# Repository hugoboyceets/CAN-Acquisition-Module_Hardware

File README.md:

# CAN-Acquisition-Module_Hardware

It's a data acquisition module that can communicate to a PC (and to other modules) over CANbus. This allows for cheap & rugged hardware, as well as simplified wiring and long transmission distances.

At it's core is a Nuvoton M483 microcontroller (ARM Cortex-M4F). It has 8 thermistor inputs, 4 multipurpose analog inputs, and room to accomodate CO2 and/or humidity sensors over I2C or UART.

It can be configured & monitored over USB (it enumerates as a COM port adapter), and a basic screen is present to facilitate human identification and debugging.

The repository for the firmware can be found [here](https://github.com/hboyce4/CAN-Acquisition-Module_Firmware).
The repository the the PC server program can be found [here](https://github.com/hugoboyceets/CAN-Acquisition-Module_Server).

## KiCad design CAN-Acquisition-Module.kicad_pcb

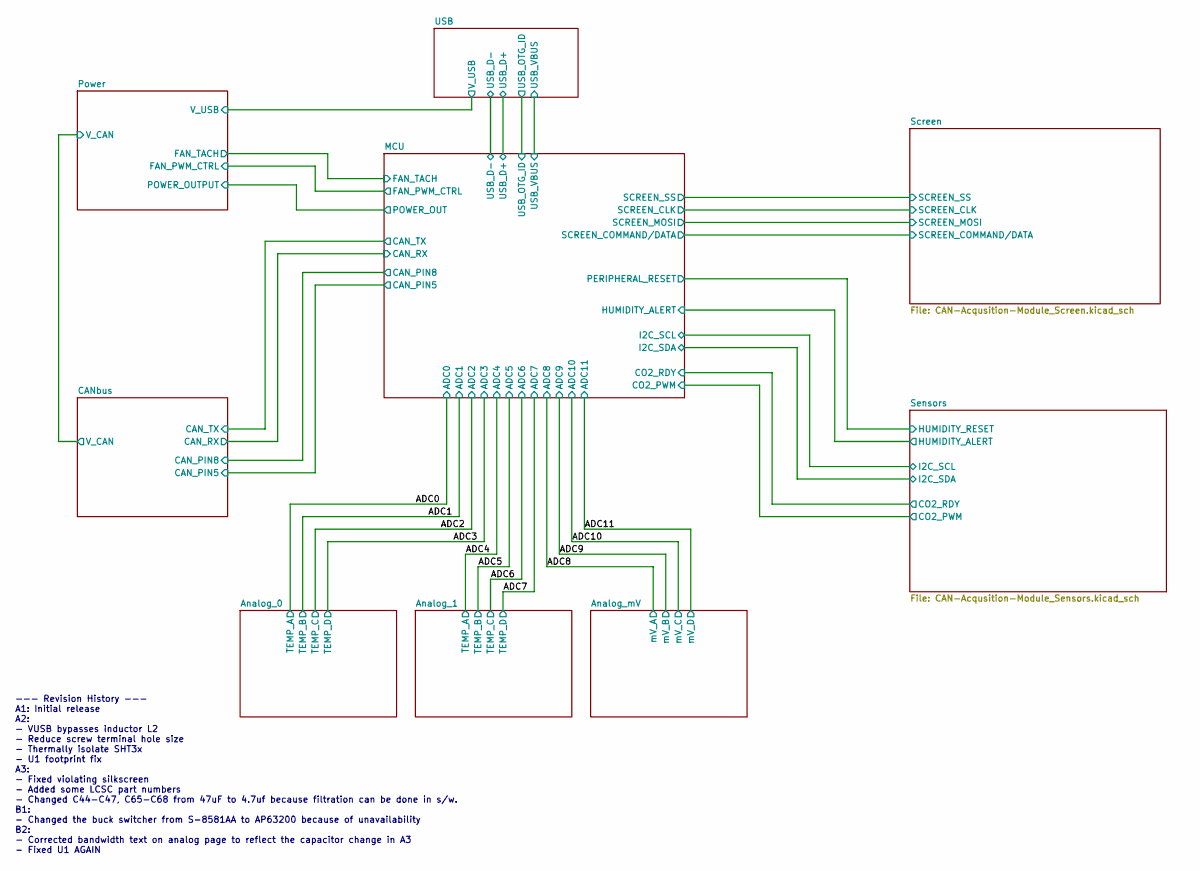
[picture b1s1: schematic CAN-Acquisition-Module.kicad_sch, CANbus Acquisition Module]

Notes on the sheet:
--- Revision History --- A1: Initial release A2: - VUSB bypasses inductor L2 - Reduce screw terminal hole size - Thermally isolate SHT3x - U1 footprint fix A3: - Fixed violating silkscreen - Added some LCSC part numbers - Changed C44-C47, C65-C68 from 47uF to 4.7uf because filtration can be done in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

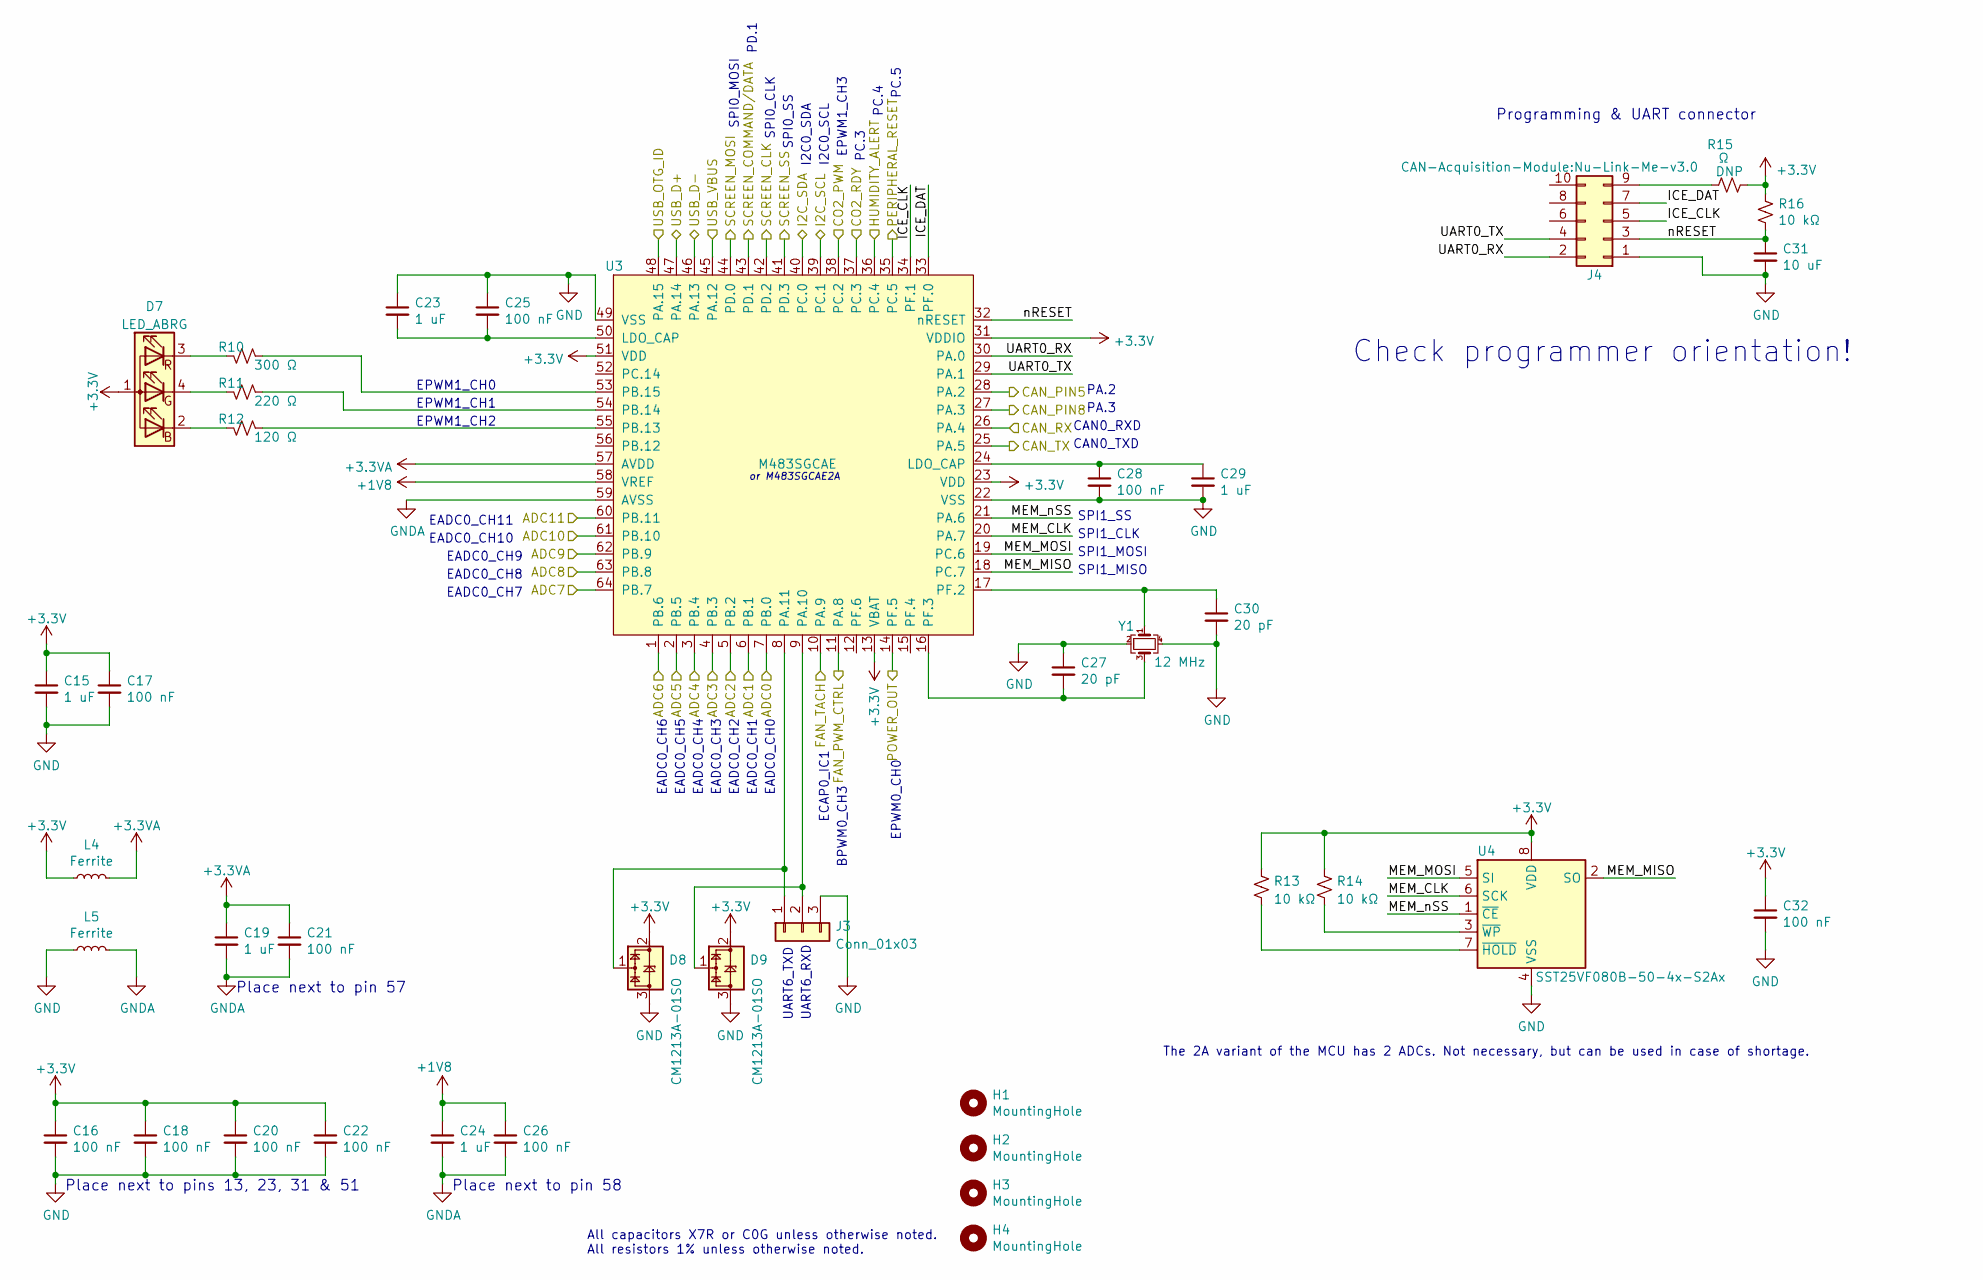
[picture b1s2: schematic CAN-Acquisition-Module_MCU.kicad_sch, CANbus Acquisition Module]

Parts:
C15, C19, C23, C24, C29: 1 uF; C_0603_1608Metric; Rated Voltage 25V; LCSC P/N C386079
C16, C17, C18, C20, C21, C22, C25, C26, C28, C32: 100 nF; C_0402_1005Metric; Rated Voltage 16V; LCSC P/N C77014
C27, C30: 20 pF; C_0603_1608Metric; LCSC P/N C123543
C31: 10 uF; C_0805_2012Metric; Rated Voltage 6.3V; LCSC P/N C386019
D7: LED_ABRG; LED_RGB_Wuerth-PLCC4_3.2x2.8mm_150141M173100; LCSC P/N C409779
D8, D9: CM1213A-01SO; SOT-23; LCSC P/N C558429
H1, H2, H3, H4: MountingHole; MountingHole_3.2mm_M3; LCSC P/N DNP
J3: Conn_01x03; PinSocket_1x03_P2.54mm_Vertical; LCSC P/N DNP
J4: Conn_02x05_Odd_Even; Nu-Link-Me-v3.0; LCSC P/N C124387
L4, L5: Ferrite; L_0603_1608Metric; LCSC P/N C96995
R10: 300 Ω; R_0603_1608Metric; Tolerance 1%; LCSC P/N C114617
R11: 220 Ω; R_0603_1608Metric; Tolerance 1%; LCSC P/N C22962
R12: 120 Ω; R_0603_1608Metric; Tolerance 1%; LCSC P/N C22787
R13, R14, R16: 10 kΩ; R_0603_1608Metric; Tolerance 1%; LCSC P/N C98220
R15: Ω; R_0603_1608Metric; LCSC P/N DNP
U3: M483SGCAE; LQFP-64_7x7mm_P0.4mm; LCSC P/N C3231235
U4: SST25VF080B-50-4x-S2Ax; SOIC-8_P1.27mm_Multi; LCSC P/N DNP
Y1: 12 MHz; Crystal_SMD_3225-4Pin_3.2x2.5mm; LCSC P/N C91749

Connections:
+1V8: C24.1, C26.1, U3.58 (VREF); also elsewhere on the board
+3.3VA: C19.1, C21.1, L4.2, U3.57 (AVDD); also elsewhere on the board
+3V3: C15.1, C16.1, C17.1, C18.1, C20.1, C22.1, C32.1, D7.1 (A), D8.2 (VP), D9.2 (VP), L4.1, R13.1, R14.1, R15.2, R16.1, U3.13 (VBAT), U3.23 (VDD), U3.31 (VDDIO), U3.51 (VDD), U4.8 (VDD); also elsewhere on the board
/ADC0: U3.7 (PB.0); also elsewhere on the board
/ADC1: U3.6 (PB.1); also elsewhere on the board
/ADC2: U3.5 (PB.2); also elsewhere on the board
/ADC3: U3.4 (PB.3); also elsewhere on the board
/ADC4: U3.3 (PB.4); also elsewhere on the board
/ADC5: U3.2 (PB.5); also elsewhere on the board
/ADC6: U3.1 (PB.6); also elsewhere on the board
/ADC7: U3.64 (PB.7); also elsewhere on the board
/ADC8: U3.63 (PB.8); also elsewhere on the board
/ADC9: U3.62 (PB.9); also elsewhere on the board
/ADC10: U3.61 (PB.10); also elsewhere on the board
/ADC11: U3.60 (PB.11); also elsewhere on the board
/CANbus/CAN_PIN5: U3.28 (PA.2); also elsewhere on the board
/CANbus/CAN_PIN8: U3.27 (PA.3); also elsewhere on the board
/CANbus/CAN_RX: U3.26 (PA.4); also elsewhere on the board
/CANbus/CAN_TX: U3.25 (PA.5); also elsewhere on the board
/MCU/CO2_PWM: U3.38 (PC.2); also elsewhere on the board
/MCU/CO2_RDY: U3.37 (PC.3); also elsewhere on the board
/MCU/FAN_PWM_CTRL: U3.11 (PA.8); also elsewhere on the board
/MCU/FAN_TACH: U3.10 (PA.9); also elsewhere on the board
/MCU/HUMIDITY_ALERT: U3.36 (PC.4); also elsewhere on the board
/MCU/I2C_SCL: U3.39 (PC.1); also elsewhere on the board
/MCU/I2C_SDA: U3.40 (PC.0); also elsewhere on the board
/MCU/ICE_CLK: J4.5, U3.34 (PF.1)
/MCU/ICE_DAT: J4.7, U3.33 (PF.0)
/MCU/MEM_CLK: U3.20 (PA.7), U4.6 (SCK)
/MCU/MEM_MISO: U3.18 (PC.7), U4.2 (SO)
/MCU/MEM_MOSI: U3.19 (PC.6), U4.5 (SI)
/MCU/MEM_nSS: U3.21 (PA.6), U4.1 (~CE)
/MCU/PERIPHERAL_RESET: U3.35 (PC.5); also elsewhere on the board
/MCU/POWER_OUT: U3.14 (PF.5); also elsewhere on the board
/MCU/SCREEN_CLK: U3.42 (PD.2); also elsewhere on the board
/MCU/SCREEN_COMMAND/DATA: U3.43 (PD.1); also elsewhere on the board
/MCU/SCREEN_MOSI: U3.44 (PD.0); also elsewhere on the board
/MCU/SCREEN_SS: U3.41 (PD.3); also elsewhere on the board
/MCU/UART0_RX: J4.2, U3.30 (PA.0)
/MCU/UART0_TX: J4.4, U3.29 (PA.1)
/MCU/USB_D+: U3.47 (PA.14); also elsewhere on the board
/MCU/USB_D-: U3.46 (PA.13); also elsewhere on the board
/MCU/USB_OTG_ID: U3.48 (PA.15); also elsewhere on the board
/MCU/USB_VBUS: U3.45 (PA.12); also elsewhere on the board
/MCU/nRESET: C31.1, J4.3, R16.2, U3.32 (nRESET)
GND: C15.2, C16.2, C17.2, C18.2, C20.2, C22.2, C23.1, C25.1, C27.1, C28.2, C29.2, C30.2, C31.2, C32.2, D8.3 (VN), D9.3 (VN), J3.3, J4.1, L5.1, U3.22 (VSS), U3.49 (VSS), U4.4 (VSS), Y1.2, Y1.4; also elsewhere on the board
GNDA: C19.2, C21.2, C24.2, C26.2, L5.2, U3.59 (AVSS); also elsewhere on the board
unnamed: C23.2, C25.2, U3.50 (LDO_CAP)
unnamed: C27.2, U3.16 (PF.3), Y1.3
unnamed: C28.1, C29.1, U3.24 (LDO_CAP)
unnamed: C30.1, U3.17 (PF.2), Y1.1
unnamed: D7.2 (BK), R12.2
unnamed: D7.3 (RK), R10.2
unnamed: D7.4 (GK), R11.2
unnamed: D8.1 (CH1), J3.1, U3.8 (PA.11)
unnamed: D9.1 (CH1), J3.2, U3.9 (PA.10)
unnamed: J4.9, R15.1
unnamed: R10.1, U3.53 (PB.15)
unnamed: R11.1, U3.54 (PB.14)
unnamed: R12.1, U3.55 (PB.13)
unnamed: R13.2, U4.7 (~HOLD)
unnamed: R14.2, U4.3 (~WP)

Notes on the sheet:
PD.1
I2C0_SDA
SPI1_CLK
Programming & UART connector
PA.3
EADC0_CH9
EPWM1_CH3
EADC0_CH5
Place next to pins 13, 23, 31 & 51
EADC0_CH10
SPI0_SS
The 2A variant of the MCU has 2 ADCs. Not necessary, but can be used in case of shortage.
EPWM1_CH0
PC.5
PC.3
EADC0_CH6
ECAP0_IC1
CAN0_RXD
CAN0_TXD
Place next to pin 58
SPI0_MOSI
EADC0_CH0
Check programmer orientation!
UART6_RXD
PC.4
EPWM1_CH1
UART6_TXD
All capacitors X7R or C0G unless otherwise noted. All resistors 1% unless otherwise noted.
Place next to pin 57
EPWM0_CH0
SPI1_MISO
EADC0_CH7
or M483SGCAE2A
BPWM0_CH3
EADC0_CH8
EADC0_CH1
EADC0_CH2
EPWM1_CH2
EADC0_CH4
SPI0_CLK

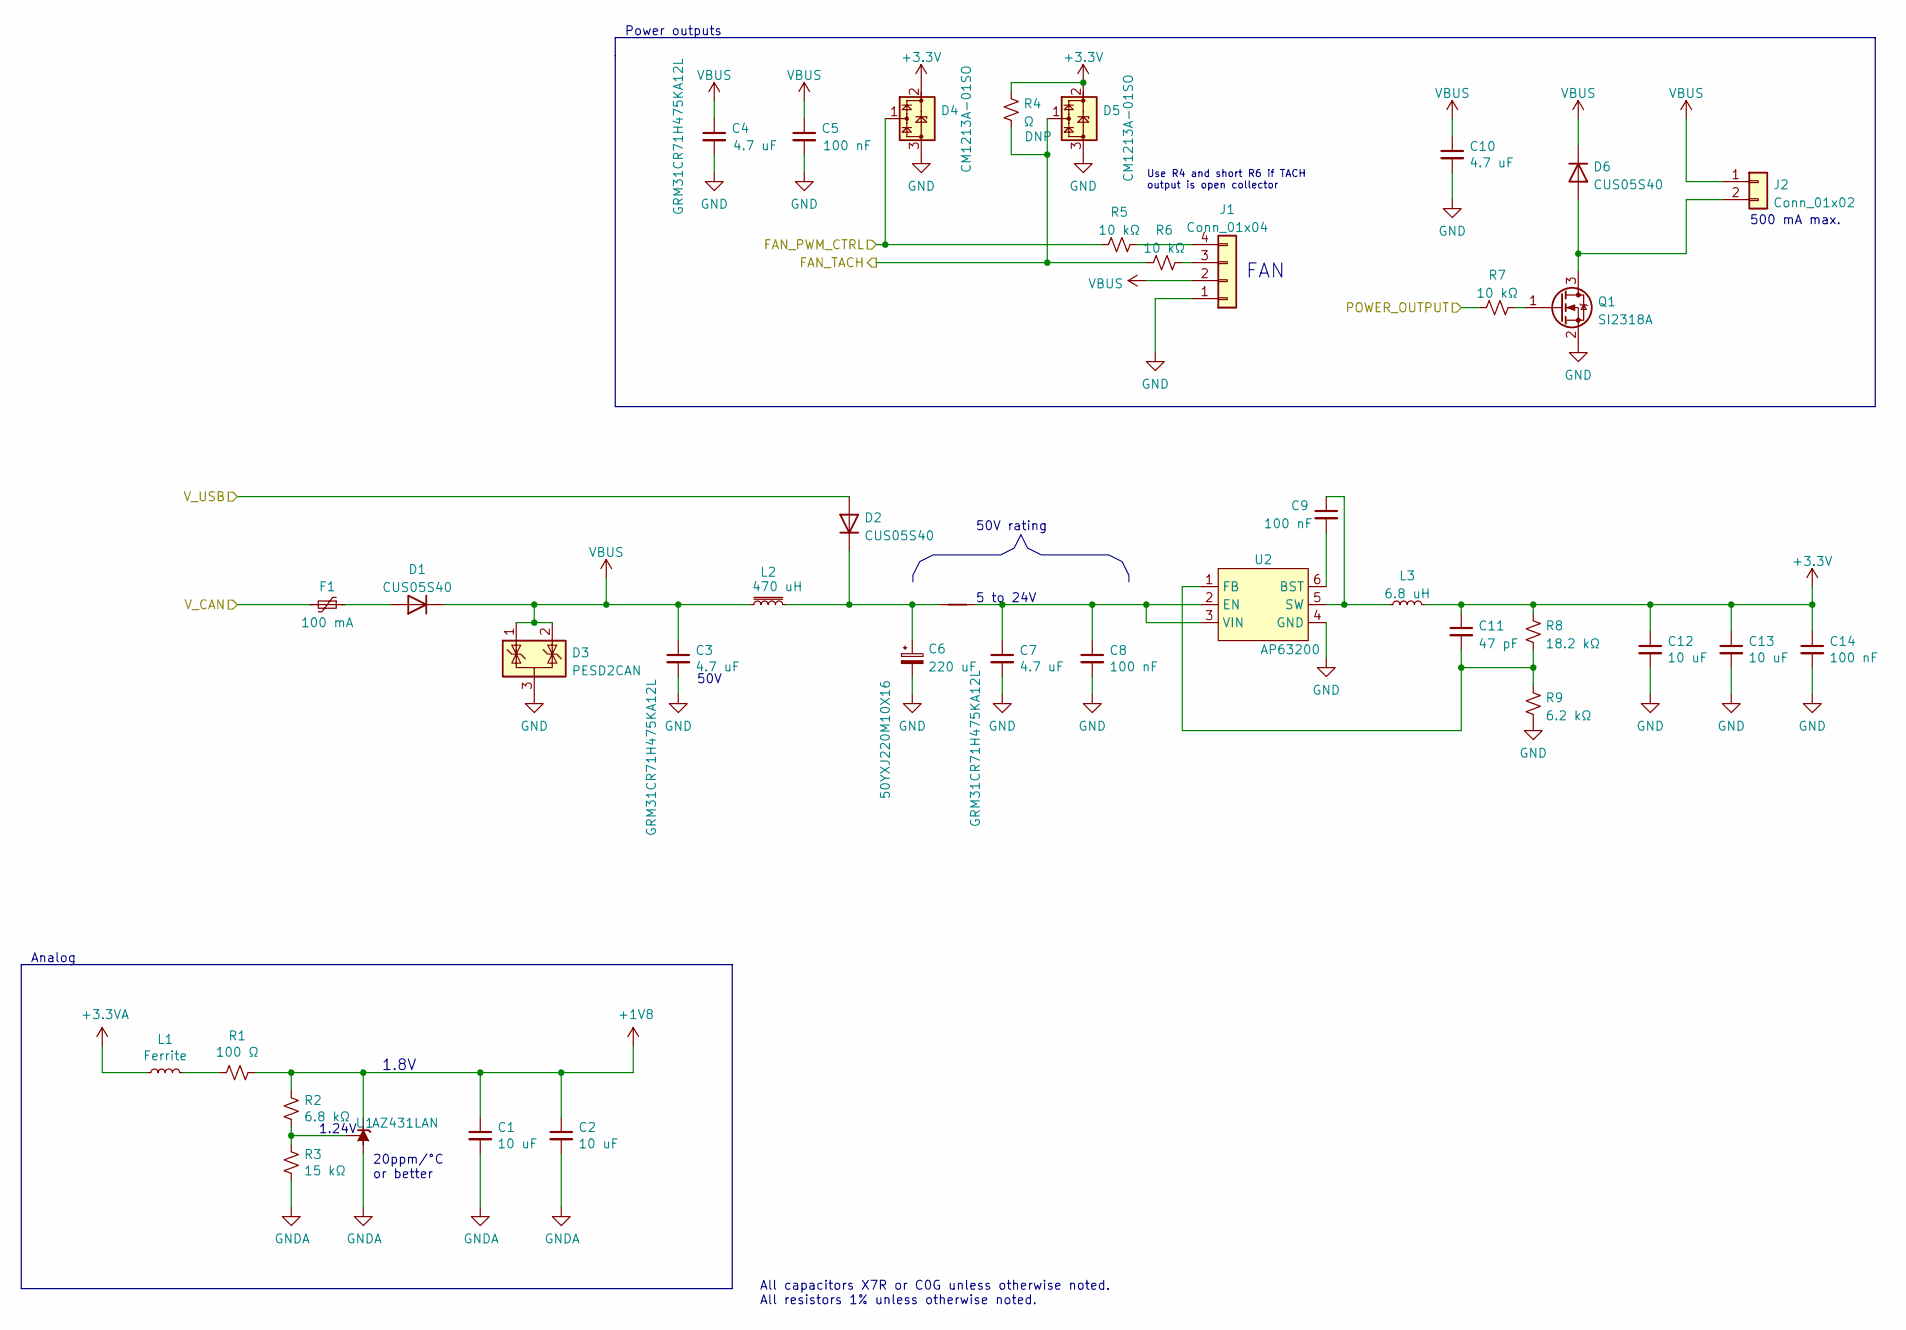
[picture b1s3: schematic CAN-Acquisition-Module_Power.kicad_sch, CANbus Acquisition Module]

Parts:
C1, C2, C12, C13: 10 uF; C_0805_2012Metric; Rated Voltage 6.3V; LCSC P/N C386019
C3, C4, C7, C10: 4.7 uF; C_1206_3216Metric; Rated Voltage 50V; LCSC P/N C92853
C5, C8, C9: 100 nF; C_0603_1608Metric; Rated Voltage 50V; LCSC P/N C314282
C6: 220 uF; CP_Radial_D10.0mm_P5.00mm_Horizontal; Rated Voltage 50V; LCSC P/N DNP
C11: 47 pF; C_0603_1608Metric; LCSC P/N C126580
C14: 100 nF; C_0402_1005Metric; Rated Voltage 16V; LCSC P/N C77014
D1, D2, D6: CUS05S40; Toshiba_USC; LCSC P/N C2762696
D3: PESD2CAN; SOT-23; LCSC P/N C284078
D4, D5: CM1213A-01SO; SOT-23; LCSC P/N C558429
F1: 100 mA; Fuse_1206_3216Metric; LCSC P/N C70065
J1: Conn_01x04; FanPinHeader_1x04_P2.54mm_Vertical; LCSC P/N DNP
J2: Conn_01x02; PinHeader_1x02_P2.54mm_Vertical; LCSC P/N DNP
L1: Ferrite; L_0603_1608Metric; LCSC P/N C96995
L2: 470 uH; Murata_LQH43_1812(4532_Metric); LCSC P/N C394141
L3: 6.8 uH; Murata_LQH3_1212(3030_Metric); LCSC P/N C703775
NT1: NetTie_2; Net_Tie_small; LCSC P/N DNP
Q1: SI2318A; SOT-23; LCSC P/N DNP
R1: 100 Ω; R_0805_2012Metric; Tolerance 5%; LCSC P/N C17408
R2: 6.8 kΩ; R_0603_1608Metric; Tolerance 0.1%; LCSC P/N C55912
R3: 15 kΩ; R_0603_1608Metric; Tolerance 0.1%; LCSC P/N C60590
R4: Ω; R_0603_1608Metric; LCSC P/N DNP
R5, R6, R7: 10 kΩ; R_0603_1608Metric; Tolerance 1%; LCSC P/N C98220
R8: 18.2 kΩ; R_0603_1608Metric; Tolerance 1%; LCSC P/N C22892
R9: 6.2 kΩ; R_0805_2012Metric; Tolerance 0.1%; LCSC P/N C351551
U1: AZ431LAN; SOT-23; LCSC P/N C460576
U2: AP63200; Diodes-Inc_TSOT26; LCSC P/N C2071868

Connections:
+1V8: C1.1, C2.1, R1.1, R2.1, U1.2 (K); also elsewhere on the board
+3.3VA: L1.1; also elsewhere on the board
+3V3: C11.1, C12.1, C13.1, C14.1, D4.2 (VP), D5.2 (VP), L3.2, R4.2, R8.1; also elsewhere on the board
/CANbus/V+/RED: F1.2; also elsewhere on the board
/MCU/FAN_PWM_CTRL: D4.1 (CH1), R5.1; also elsewhere on the board
/MCU/FAN_TACH: D5.1 (CH1), R4.1, R6.1; also elsewhere on the board
/MCU/POWER_OUT: R7.1; also elsewhere on the board
/Power/V_USB: D2.2 (A); also elsewhere on the board
GND: C3.2, C4.2, C5.2, C6.2, C7.2, C8.2, C10.2, C12.2, C13.2, C14.2, D3.3 (A), D4.3 (VN), D5.3 (VN), J1.1, Q1.2 (S), R9.2, U2.4 (GND); also elsewhere on the board
GNDA: C1.2, C2.2, R3.2, U1.3 (A); also elsewhere on the board
unnamed: C6.1, D2.1 (K), L2.2, NT1.1
unnamed: C7.1, C8.1, NT1.2, U2.2 (EN), U2.3 (VIN)
unnamed: C9.1, L3.1, U2.5 (SW)
unnamed: C9.2, U2.6 (BST)
unnamed: C11.2, R8.2, R9.1, U2.1 (FB)
unnamed: D1.2 (A), F1.1
unnamed: D6.2 (A), J2.2, Q1.3 (D)
unnamed: J1.3, R6.2
unnamed: J1.4, R5.2
unnamed: L1.2, R1.2
unnamed: Q1.1 (G), R7.2
unnamed: R2.2, R3.1, U1.1 (REF)
VBUS: C3.1, C4.1, C5.1, C10.1, D1.1 (K), D3.1 (K), D3.2 (K), D6.1 (K), J1.2, J2.1, L2.1

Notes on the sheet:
50V
5 to 24V
1.8V
FAN
Power outputs
Analog
All capacitors X7R or C0G unless otherwise noted. All resistors 1% unless otherwise noted.
Use R4 and short R6 if TACH output is open collector
1.24V
50V rating
500 mA max.
20ppm/°C or better

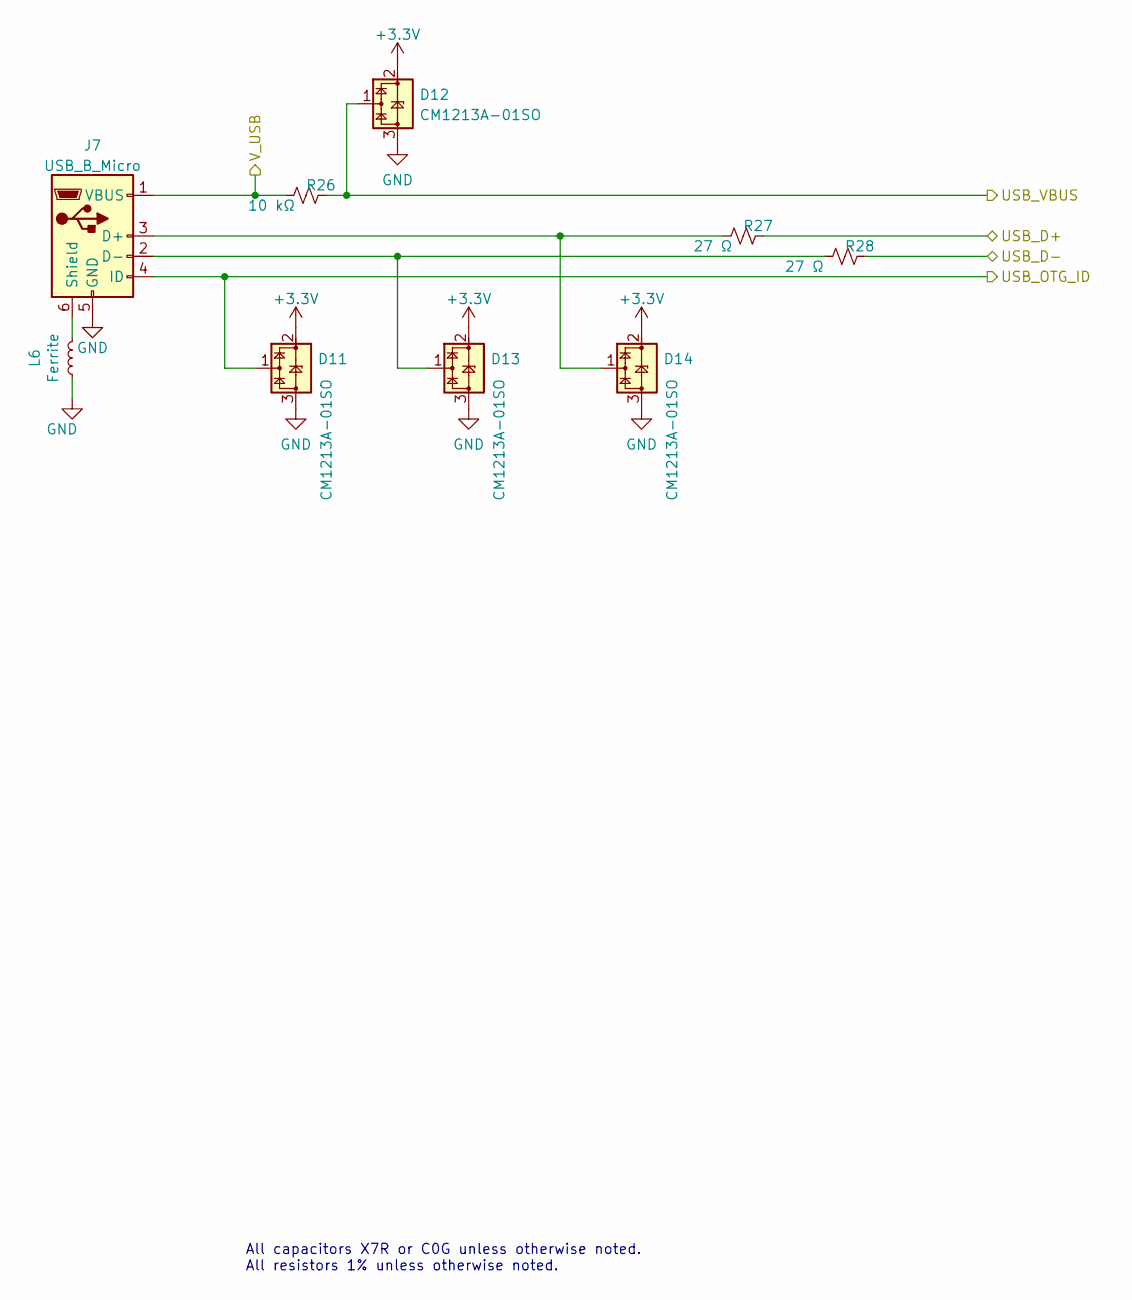
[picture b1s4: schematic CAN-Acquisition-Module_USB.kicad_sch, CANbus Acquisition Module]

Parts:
D11, D12, D13, D14: CM1213A-01SO; SOT-23; LCSC P/N C558429
J7: USB_B_Micro; GCT-USB3131-30-0230-A; LCSC P/N C920231
L6: Ferrite; L_0603_1608Metric; LCSC P/N C96995
R26: 10 kΩ; R_0603_1608Metric; Tolerance 1%; LCSC P/N C98220
R27, R28: 27 Ω; R_0603_1608Metric; Tolerance 1%; LCSC P/N C25190

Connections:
+3V3: D11.2 (VP), D12.2 (VP), D13.2 (VP), D14.2 (VP); also elsewhere on the board
/MCU/USB_D+: R27.2; also elsewhere on the board
/MCU/USB_D-: R28.2; also elsewhere on the board
/MCU/USB_OTG_ID: D11.1 (CH1), J7.4 (ID); also elsewhere on the board
/MCU/USB_VBUS: D12.1 (CH1), R26.2; also elsewhere on the board
/Power/V_USB: J7.1 (VBUS), R26.1; also elsewhere on the board
GND: D11.3 (VN), D12.3 (VN), D13.3 (VN), D14.3 (VN), J7.5 (GND), L6.1; also elsewhere on the board
unnamed: D13.1 (CH1), J7.2 (D-), R28.1
unnamed: D14.1 (CH1), J7.3 (D+), R27.1
unnamed: J7.6 (Shield), L6.2

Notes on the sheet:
All capacitors X7R or C0G unless otherwise noted. All resistors 1% unless otherwise noted.

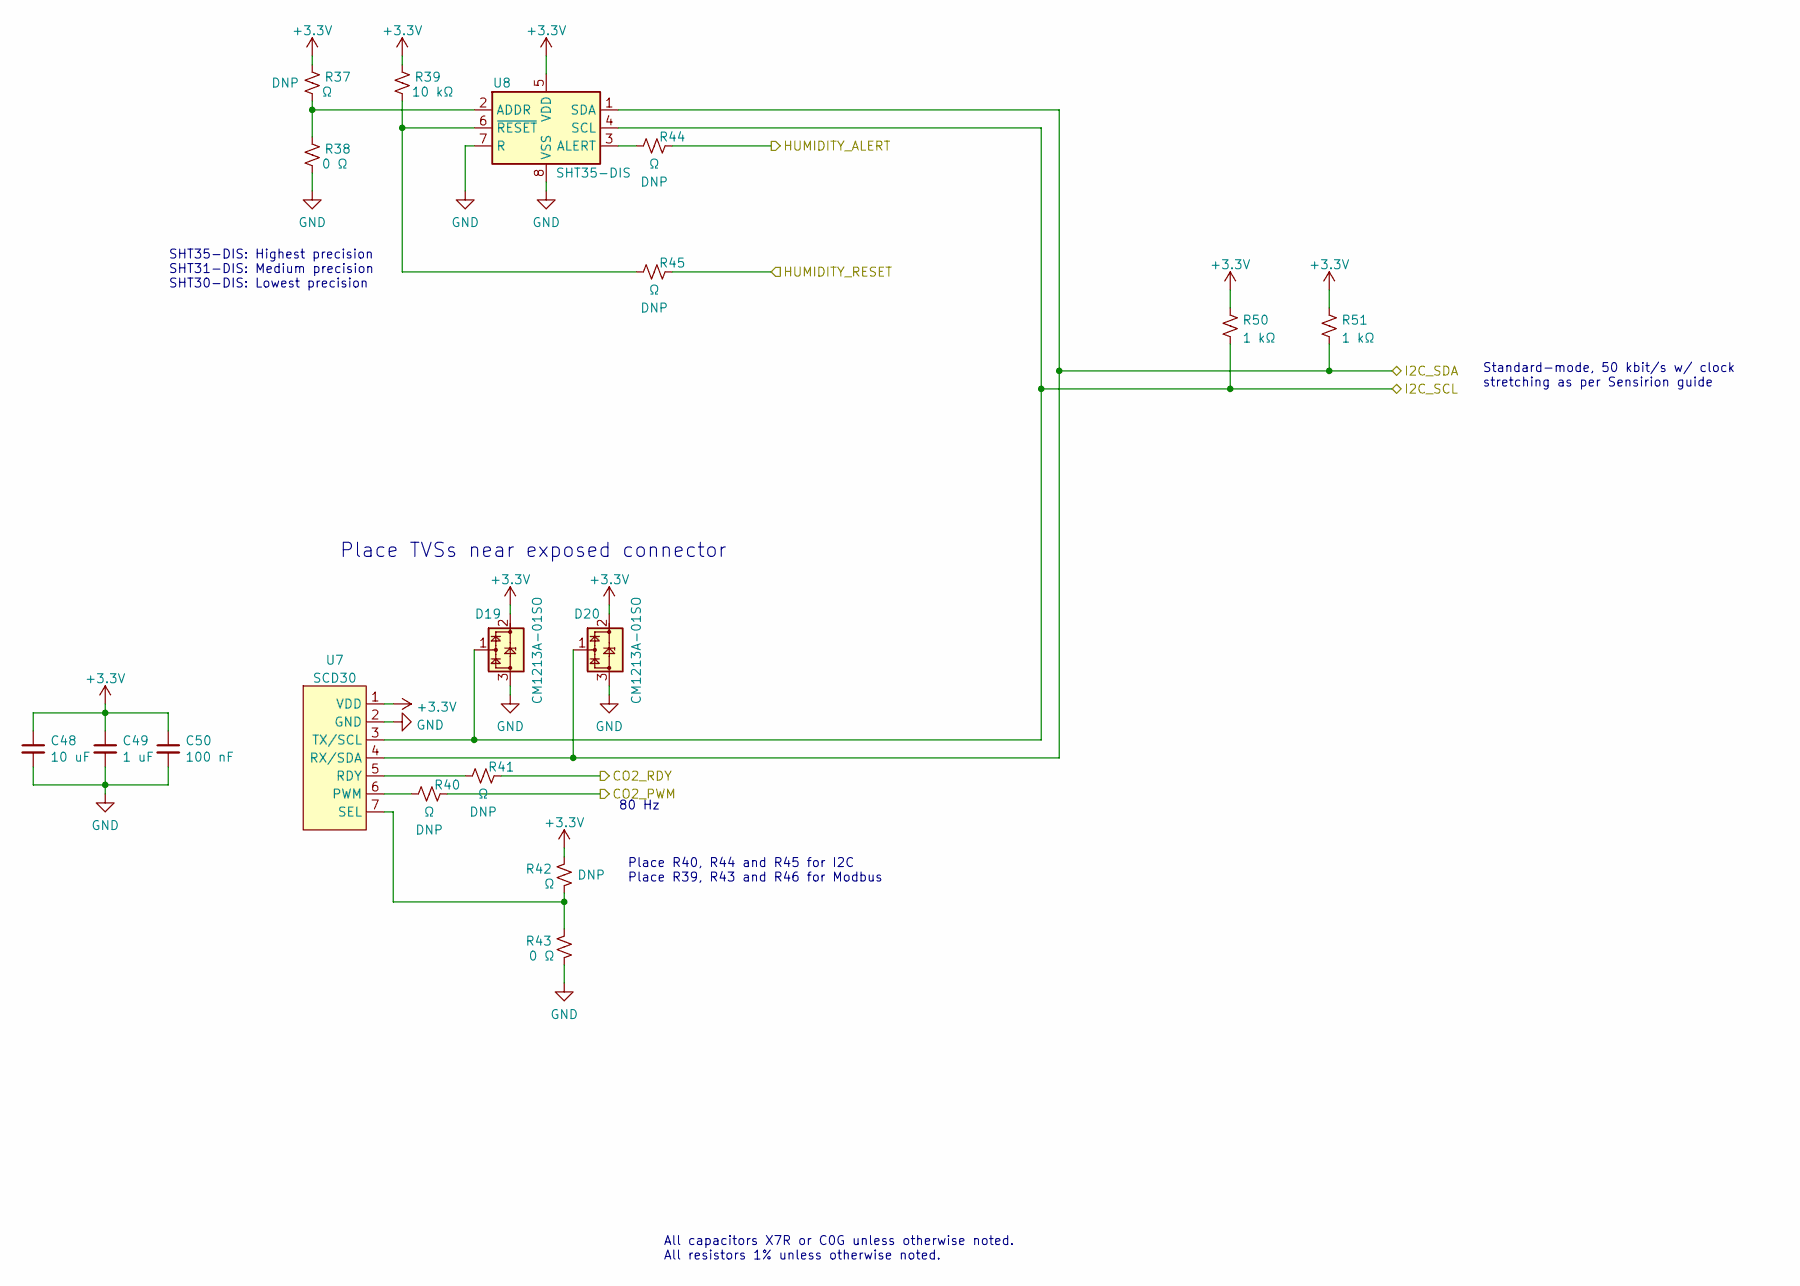
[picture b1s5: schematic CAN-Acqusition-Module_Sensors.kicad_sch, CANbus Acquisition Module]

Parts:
C48: 10 uF; C_0805_2012Metric; Rated Voltage 6.3V; LCSC P/N C386019
C49: 1 uF; C_0603_1608Metric; Rated Voltage 25V; LCSC P/N C386079
C50: 100 nF; C_0402_1005Metric; Rated Voltage 16V; LCSC P/N C77014
D19, D20: CM1213A-01SO; SOT-23; LCSC P/N C558429
R37, R40, R41, R42, R44, R45: Ω; R_0603_1608Metric; LCSC P/N DNP
R38, R43: 0 Ω; R_0603_1608Metric; Tolerance 1%; LCSC P/N C21189
R39: 10 kΩ; R_0603_1608Metric; Tolerance 1%; LCSC P/N C98220
R50, R51: 1 kΩ; R_0603_1608Metric; Tolerance 1%; LCSC P/N C22548
U7: SCD30; LCSC P/N DNP
U8: SHT35-DIS; Sensirion_DFN-8-1EP_2.5x2.5mm_P0.5mm_EP1.1x1.7mm; LCSC P/N DNP

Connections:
+3V3: C48.1, C49.1, C50.1, D19.2 (VP), D20.2 (VP), R37.1, R39.1, R42.1, R50.1, R51.1, U7.1 (VDD), U8.5 (VDD); also elsewhere on the board
/MCU/CO2_PWM: R40.2; also elsewhere on the board
/MCU/CO2_RDY: R41.2; also elsewhere on the board
/MCU/HUMIDITY_ALERT: R44.2; also elsewhere on the board
/MCU/I2C_SCL: D19.1 (CH1), R50.2, U7.3 (TX/SCL), U8.4 (SCL); also elsewhere on the board
/MCU/I2C_SDA: D20.1 (CH1), R51.2, U7.4 (RX/SDA), U8.1 (SDA); also elsewhere on the board
/MCU/PERIPHERAL_RESET: R45.2; also elsewhere on the board
GND: C48.2, C49.2, C50.2, D19.3 (VN), D20.3 (VN), R38.2, R43.2, U7.2 (GND), U8.7 (R), U8.8 (VSS), U8.9 (VSS); also elsewhere on the board
unnamed: R37.2, R38.1, U8.2 (ADDR)
unnamed: R39.2, R45.1, U8.6 (~RESET)
unnamed: R40.1, U7.6 (PWM)
unnamed: R41.1, U7.5 (RDY)
unnamed: R42.2, R43.1, U7.7 (SEL)
unnamed: R44.1, U8.3 (ALERT)

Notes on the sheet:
80 Hz
SHT35-DIS: Highest precision SHT31-DIS: Medium precision SHT30-DIS: Lowest precision
All capacitors X7R or C0G unless otherwise noted. All resistors 1% unless otherwise noted.
Place R40, R44 and R45 for I2C Place R39, R43 and R46 for Modbus
Standard-mode, 50 kbit/s w/ clock stretching as per Sensirion guide
Place TVSs near exposed connector

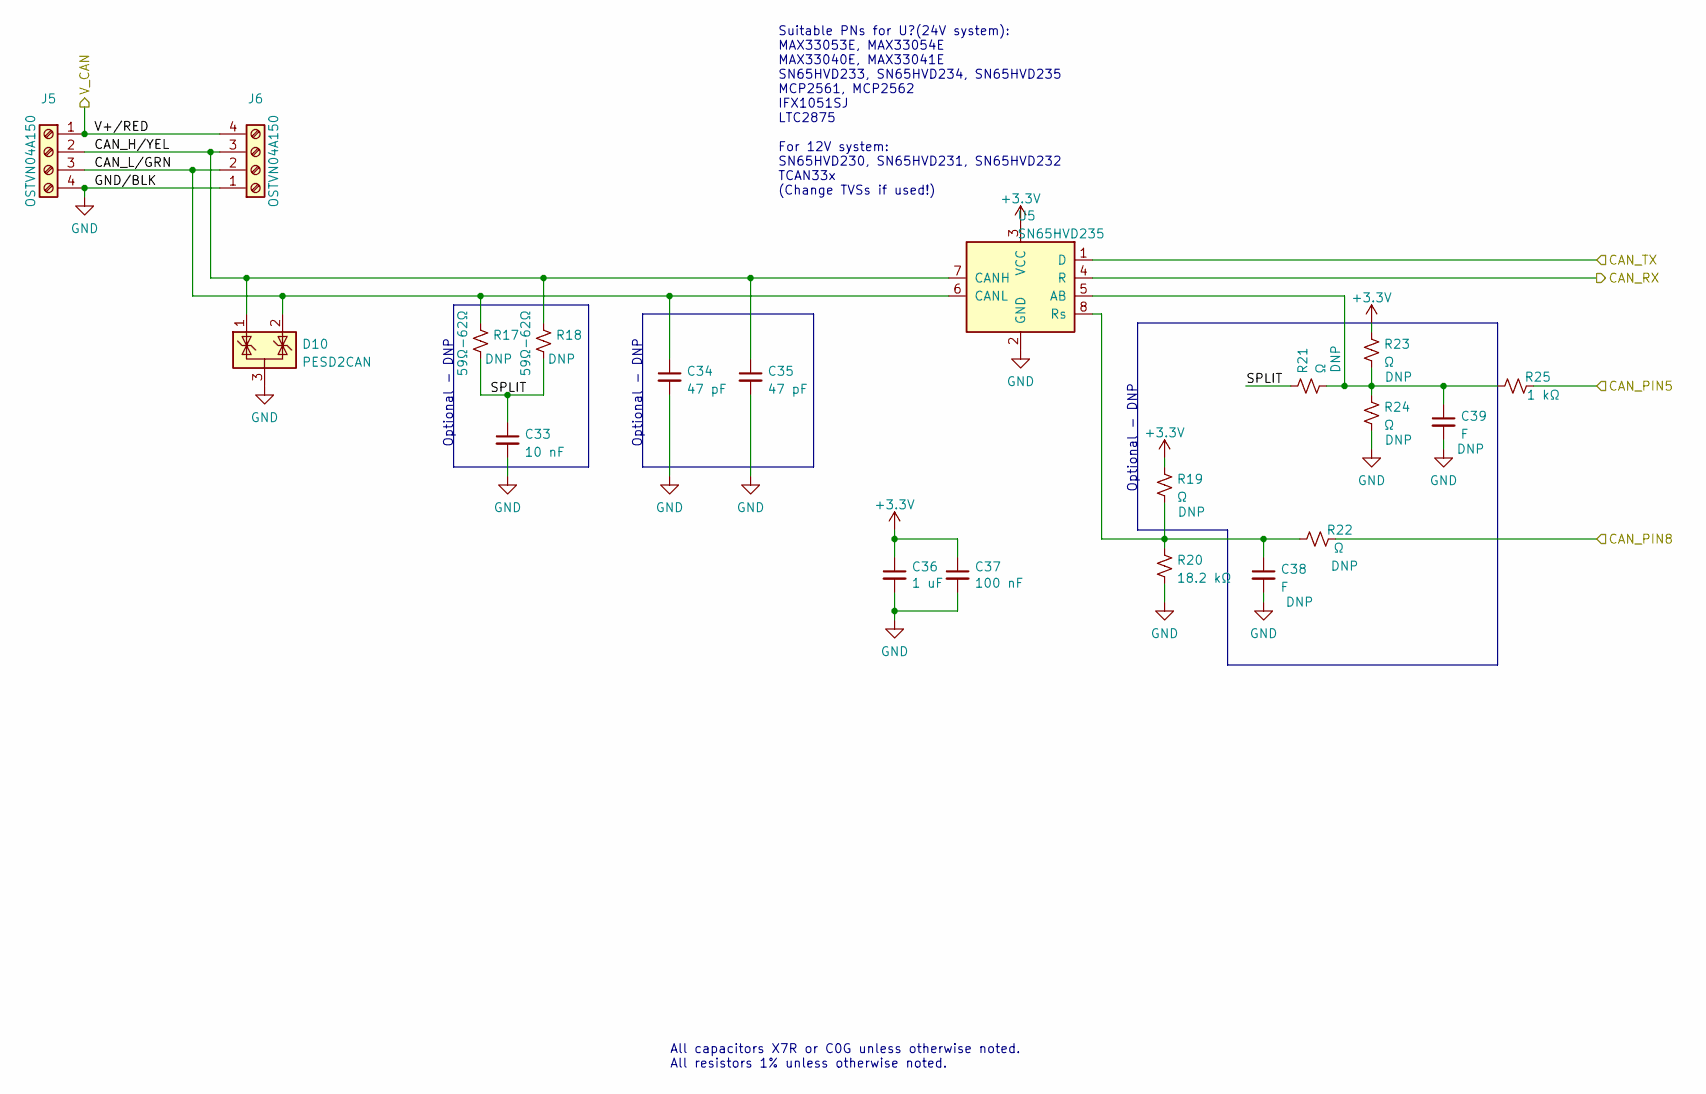
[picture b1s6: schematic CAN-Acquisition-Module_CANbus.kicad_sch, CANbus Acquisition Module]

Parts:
C33: 10 nF; C_0603_1608Metric; LCSC P/N DNP
C34, C35: 47 pF; C_0603_1608Metric; LCSC P/N C126580
C36: 1 uF; C_0603_1608Metric; Rated Voltage 25V; LCSC P/N C386079
C37: 100 nF; C_0402_1005Metric; Rated Voltage 16V; LCSC P/N C77014
C38, C39: F; C_0603_1608Metric; LCSC P/N DNP
D10: PESD2CAN; SOT-23; LCSC P/N C284078
J5, J6: OSTVN04A150; LCSC P/N C708735
R17, R18: 59Ω-62Ω; R_1206_3216Metric; LCSC P/N DNP
R19, R21, R22, R23, R24: Ω; R_0603_1608Metric; LCSC P/N DNP
R20: 18.2 kΩ; R_0603_1608Metric; Tolerance 1%; LCSC P/N C22892
R25: 1 kΩ; R_0603_1608Metric; Tolerance 1%; LCSC P/N C22548
U5: SN65HVD235; SOIC-8_3.9x4.9mm_P1.27mm; LCSC P/N C111810

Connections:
+3V3: C36.1, C37.1, R19.1, R23.1, U5.3 (VCC); also elsewhere on the board
/CANbus/CAN_H/YEL: C35.1, D10.1 (K), J5.2, J6.3, R18.1, U5.7 (CANH)
/CANbus/CAN_L/GRN: C34.1, D10.2 (K), J5.3, J6.2, R17.1, U5.6 (CANL)
/CANbus/CAN_PIN5: R25.2; also elsewhere on the board
/CANbus/CAN_PIN8: R22.2; also elsewhere on the board
/CANbus/CAN_RX: U5.4 (R); also elsewhere on the board
/CANbus/CAN_TX: U5.1 (D); also elsewhere on the board
/CANbus/SPLIT: C33.1, R17.2, R18.2, R21.1
/CANbus/V+/RED: J5.1, J6.4; also elsewhere on the board
GND: C33.2, C34.2, C35.2, C36.2, C37.2, C38.2, C39.2, D10.3 (A), J5.4, J6.1, R20.2, R24.2, U5.2 (GND); also elsewhere on the board
unnamed: C38.1, R19.2, R20.1, R22.1, U5.8 (Rs)
unnamed: C39.1, R21.2, R23.2, R24.1, R25.1, U5.5 (AB)

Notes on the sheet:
All capacitors X7R or C0G unless otherwise noted. All resistors 1% unless otherwise noted.
Optional - DNP
Suitable PNs for U?(24V system): MAX33053E, MAX33054E MAX33040E, MAX33041E SN65HVD233, SN65HVD234, SN65HVD235 MCP2561, MCP2562 IFX1051SJ LTC2875 For 12V system: SN65HVD230, SN65HVD231, SN65HVD232 TCAN33x (Change TVSs if used!)

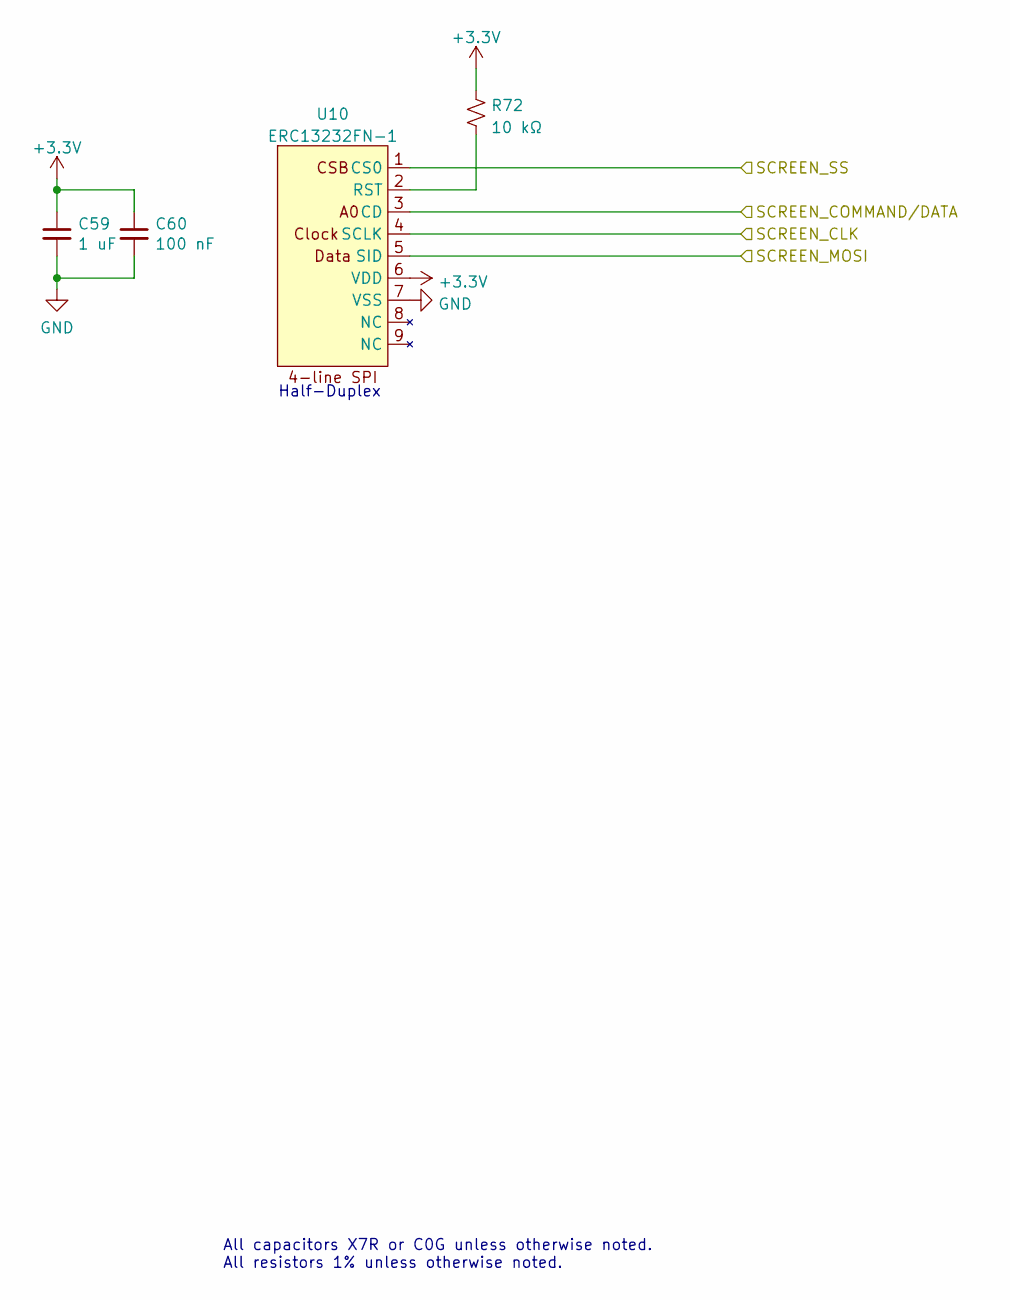
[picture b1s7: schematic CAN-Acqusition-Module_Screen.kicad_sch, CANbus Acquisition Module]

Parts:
C59: 1 uF; C_0603_1608Metric; Rated Voltage 25V; LCSC P/N C386079
C60: 100 nF; C_0402_1005Metric; Rated Voltage 16V; LCSC P/N C77014
R72: 10 kΩ; R_0603_1608Metric; Tolerance 1%; LCSC P/N C98220
U10: ERC13232FN-1; LCSC P/N DNP

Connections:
+3V3: C59.1, C60.1, R72.1, U10.6 (VDD); also elsewhere on the board
/MCU/SCREEN_CLK: U10.4 (SCLK); also elsewhere on the board
/MCU/SCREEN_COMMAND/DATA: U10.3 (CD); also elsewhere on the board
/MCU/SCREEN_MOSI: U10.5 (SID); also elsewhere on the board
/MCU/SCREEN_SS: U10.1 (CS0); also elsewhere on the board
GND: C59.2, C60.2, U10.7 (VSS); also elsewhere on the board
unnamed: R72.2, U10.2 (RST)

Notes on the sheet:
Half-Duplex
All capacitors X7R or C0G unless otherwise noted. All resistors 1% unless otherwise noted.
